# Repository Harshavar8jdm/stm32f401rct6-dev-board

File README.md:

# STM32F401RCT6 Development Board

A compact development board built around the STM32F401RCT6 microcontroller. The design provides access to core peripherals via standard pin headers, incorporates dedicated power plane isolation for analog stability, and includes robust ESD protection for reliable USB communication. 

## Visuals

### Schematic Diagram

### PCB Layout

### 3D Renders
| Front View | Back View |
| :---: | :---: |
|  |  |

---

## Features

### 1. Core Processing & Clock System
* **Microcontroller:** STM32F401RCT6, 32-bit ARM Cortex-M4 core running up to 84 MHz.
* **High-Speed External (HSE) Clock:** $25\text{ MHz}$ crystal oscillator loop supplying the primary system and peripheral clock source.
* **Low-Speed External (LSE) Clock:** $32.768\text{ kHz}$ tuning-fork crystal providing timing for the internal Real-Time Clock (RTC).
* **Reset & Boot Controls:** Hardware reset circuitry utilizing an RC network connected to the `NRST` pin, paired with a dedicated physical push-button to pull `BOOT0` high for system bootloader entry.

### 2. Power Delivery & Noise Mitigation
* **Voltage Regulation:** AMS1117-3.3 Linear Voltage Regulator (LDO) stepping down a $5\text{V}$ input supply (via USB) to a regulated $+3.3\text{V}$ system rail, decoupled with dual $22\ \mu\text{F}$ bulk capacitors.
* **Digital Rail Decoupling:** Localized filtering network consisting of one $4.7\ \mu\text{F}$ bulk capacitor and five independent $100\text{ nF}$ capacitors dedicated to the $V_{DD}$ supply pins.
* **Analog Isolation ($+3.3\text{VA}$):** A $100\ \Omega$ (at $100\text{ MHz}$) ferrite bead creates a low-pass filter to separate the analog supply from digital switching noise, supported by dedicated $1\ \mu\text{F}$ and $100\text{ nF}$ capacitors.

### 3. Connectivity & Protection
* **USB-C Interface:** USB 2.0 downstream configuration over a physical USB-C connector using dual $5.1\text{ k}\Omega$ pulldown resistors on the `CC1` and `CC2` channels.
* **Transient Voltage Protection:** A USBLC6-2SC6 monolithic ESD protection diode array is placed directly on the `USB_D+` and `USB_D-` lines to safeguard internal transceivers against electrostatic discharge.
* **Peripheral Access:** Dedicated pin headers breaking out SPI (`SPI3`), I2C (`I2C2`), UART (`UART1`), Serial Wire Debug (`SWD`), and generic GPIOs.
* **System Status:** Physical LED indicators tracking power availability ($+3.3\text{V}$) and a user-programmable diagnostic LED linked to pin `PA0`.

---

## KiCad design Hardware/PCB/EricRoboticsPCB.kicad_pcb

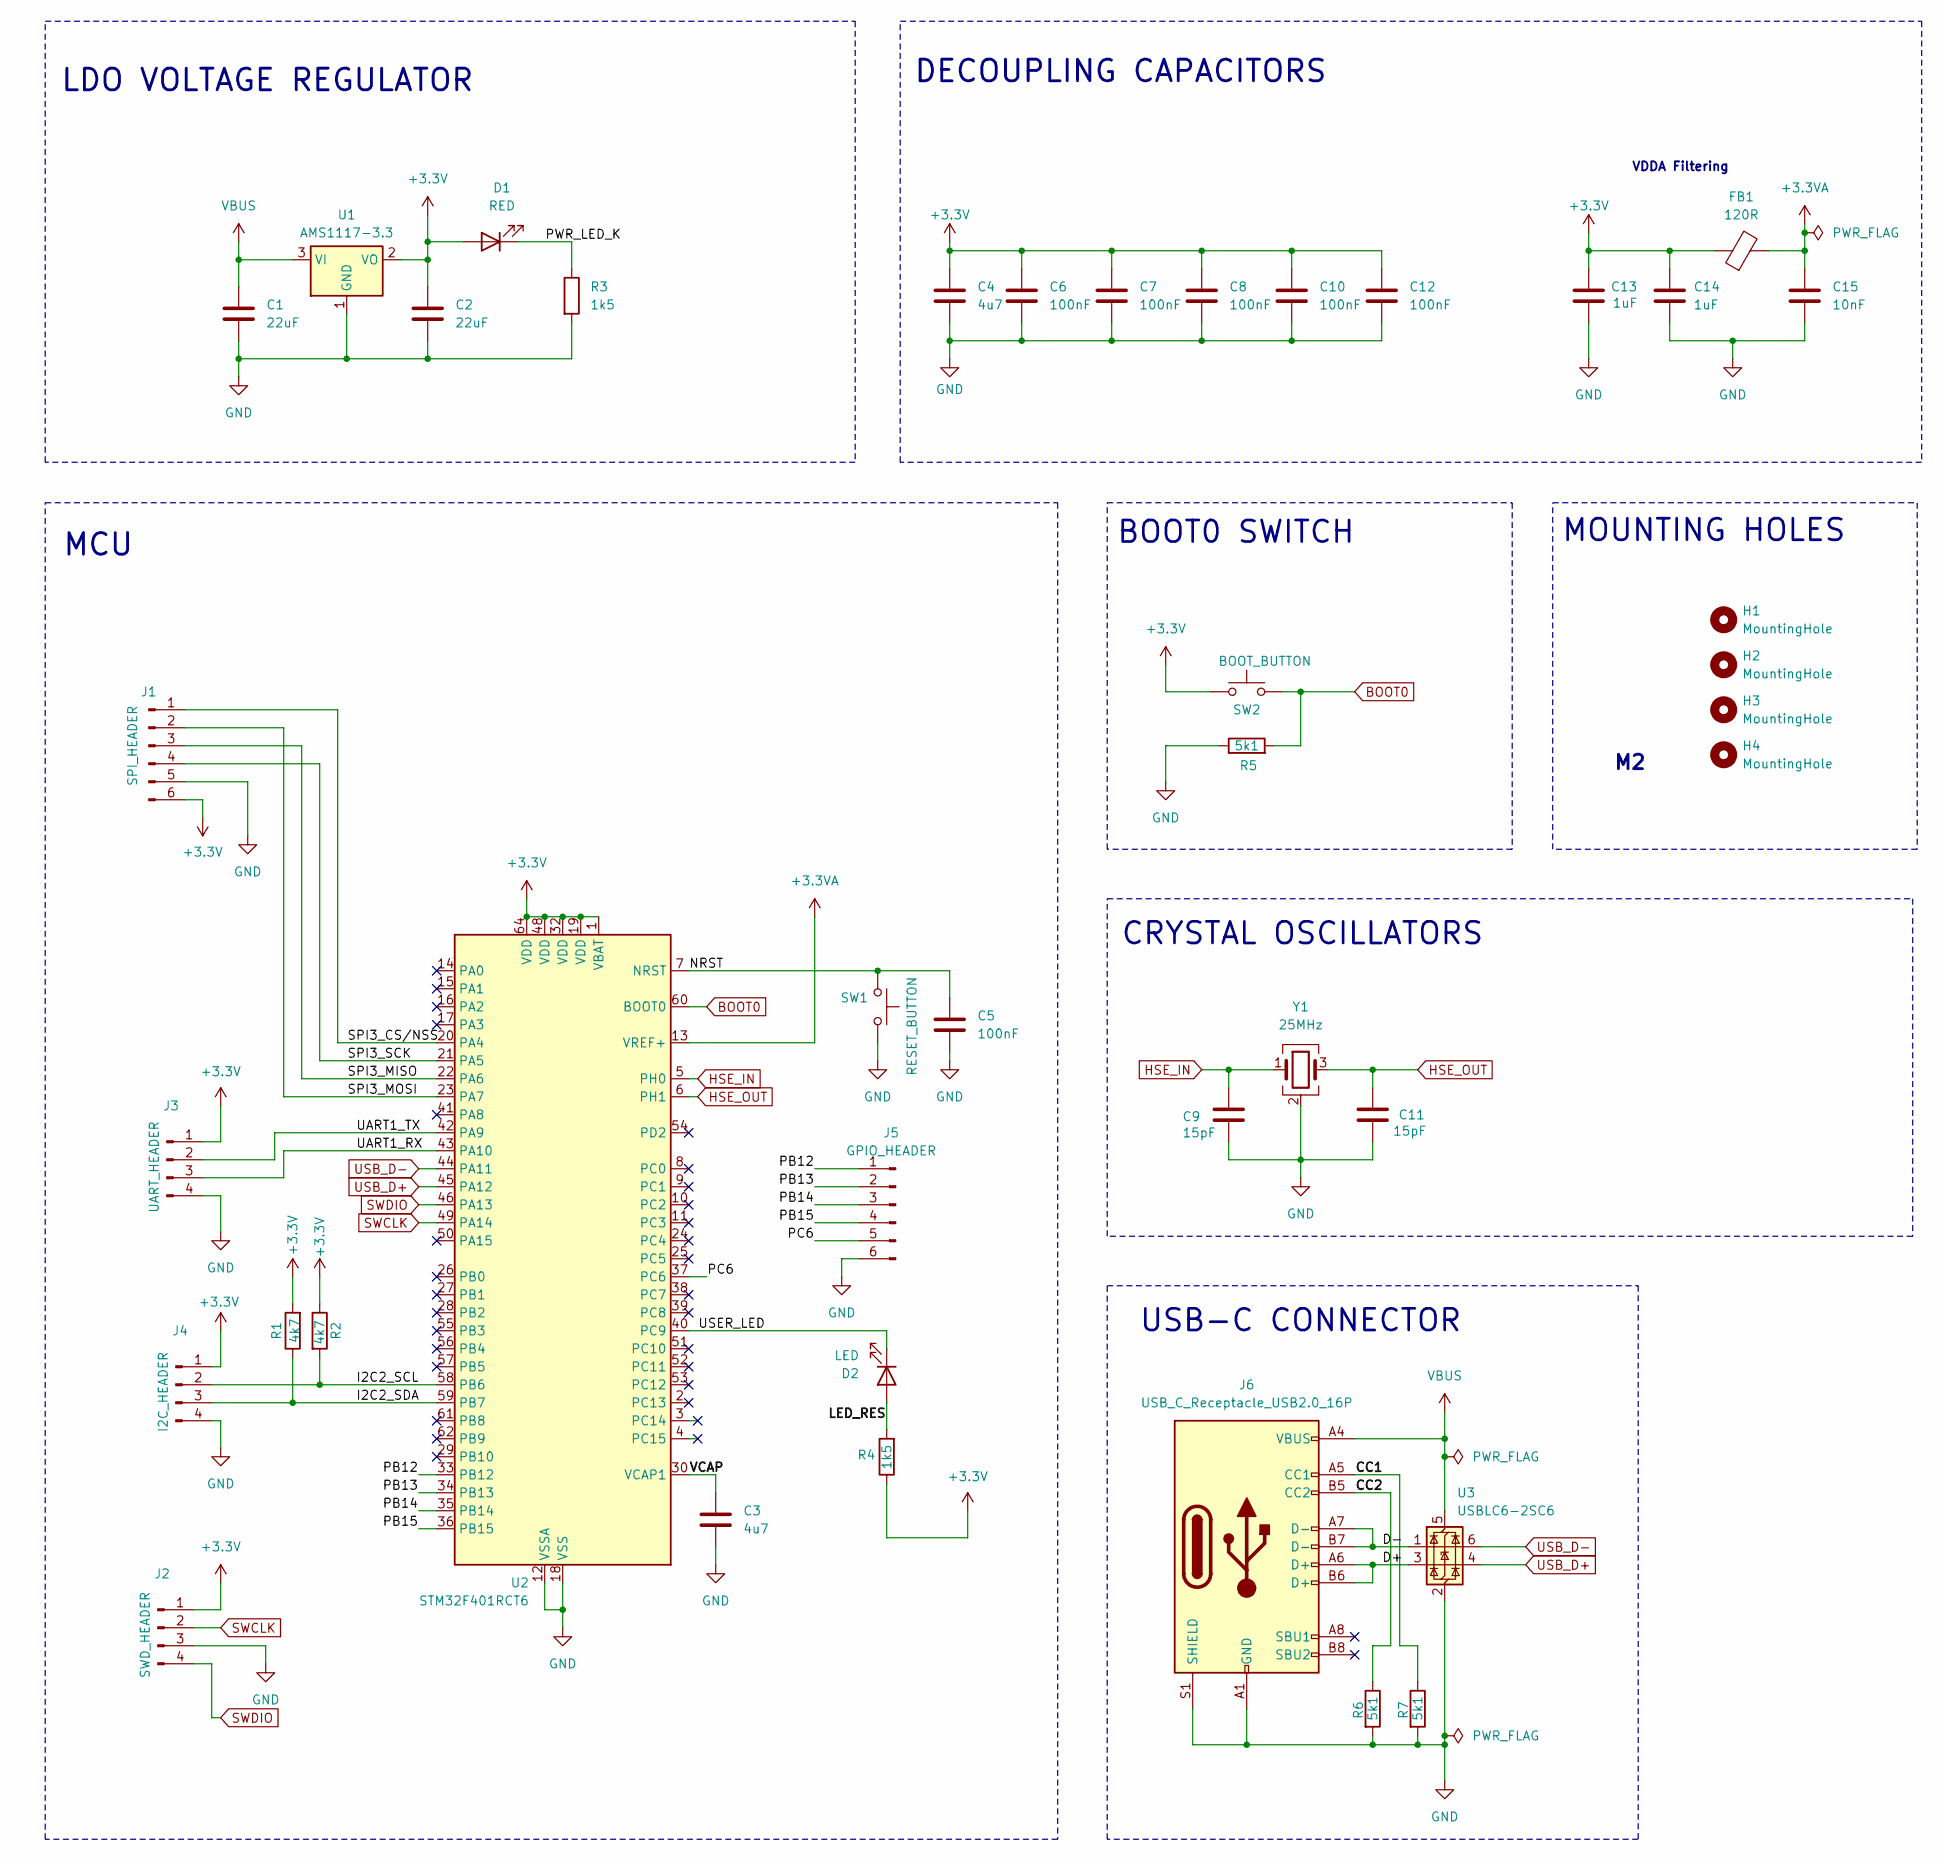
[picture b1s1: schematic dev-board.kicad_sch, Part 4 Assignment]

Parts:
C1, C2: 22uF; C_0805_2012Metric
C3, C4: 4u7; C_0805_2012Metric
C5, C6, C7, C8, C10, C12: 100nF; C_0402_1005Metric
C9, C11: 15pF; C_0402_1005Metric
C13, C14: 1uF; C_0402_1005Metric
C15: 10nF; C_0402_1005Metric
D1: RED; LED_0603_1608Metric
D2: LED; LED_0603_1608Metric
FB1: 120R; L_0603_1608Metric
H1, H2, H3, H4: MountingHole; MountingHole_2.2mm_M2
J1: SPI_HEADER; PinHeader_1x06_P2.54mm_Vertical
J2: SWD_HEADER; PinHeader_1x04_P2.54mm_Vertical
J3: UART_HEADER; PinHeader_1x04_P2.54mm_Vertical
J4: I2C_HEADER; PinHeader_1x04_P2.54mm_Vertical
J5: GPIO_HEADER; PinHeader_1x06_P2.54mm_Vertical
J6: USB_C_Receptacle_USB2.0_16P; USB_C_Receptacle_HRO_TYPE-C-31-M-12
R1, R2: 4k7; R_0402_1005Metric
R3, R4: 1k5; R_0402_1005Metric
R5, R6, R7: 5k1; R_0402_1005Metric
SW1: RESET_BUTTON; SW_Push_SPST_NO_Alps_SKRK
SW2: BOOT_BUTTON; SW_Push_SPST_NO_Alps_SKRK
U1: AMS1117-3.3; SOT-223-3_TabPin2
U2: STM32F401RCT6; LQFP-64_10x10mm_P0.5mm
U3: USBLC6-2SC6; SOT-23-6
Y1: 25MHz; Crystal_SMD_3225-4Pin_3.2x2.5mm

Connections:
+3.3V: C2.1, C4.1, C6.1, C7.1, C8.1, C10.1, C12.1, C13.1, C14.1, D1.2 (A), FB1.1, J1.6, J2.1, J3.1, J4.1, R1.2, R2.1, R4.1, SW2.2, U1.2 (VO), U2.1 (VBAT), U2.19 (VDD), U2.32 (VDD), U2.48 (VDD), U2.64 (VDD); also elsewhere on the board
+3.3VA: C15.1, FB1.2, U2.13 (VREF+)
/CC1: J6.A5 (CC1), R7.1
/CC2: J6.B5 (CC2), R6.1
/D+: J6.A6 (D+), J6.B6 (D+), U3.3 (I/O2)
/D-: J6.A7 (D-), J6.B7 (D-), U3.1 (I/O1)
/I2C2_SCL: J4.2, R2.2, U2.58 (PB6)
/I2C2_SDA: J4.3, R1.1, U2.59 (PB7)
/LED_RES: D2.2 (A), R4.2; also elsewhere on the board
/NRST: C5.1, SW1.2, U2.7 (NRST); also elsewhere on the board
/PB12: J5.1, U2.33 (PB12)
/PB13: J5.2, U2.34 (PB13)
/PB14: J5.3, U2.35 (PB14)
/PB15: J5.4, U2.36 (PB15)
/PC6: J5.5, U2.37 (PC6)
/PWR_LED_K: D1.1 (K), R3.1
/SPI3_CS/NSS: J1.1, U2.20 (PA4)
/SPI3_MISO: J1.3, U2.22 (PA6)
/SPI3_MOSI: J1.2, U2.23 (PA7)
/SPI3_SCK: J1.4, U2.21 (PA5)
/UART1_RX: J3.3, U2.43 (PA10)
/UART1_TX: J3.2, U2.42 (PA9)
/USER_LED: D2.1 (K), U2.40 (PC9); also elsewhere on the board
/VCAP: C3.1, U2.30 (VCAP1)
BOOT0: R5.2, SW2.1, U2.60 (BOOT0); also elsewhere on the board
GND: C1.2, C2.2, C3.2, C4.2, C5.2, C6.2, C7.2, C8.2, C9.2, C10.2, C11.2, C12.2, C13.2, C14.2, C15.2, J1.5, J2.3, J3.4, J4.4, J5.6, J6.A1 (GND), J6.A12 (GND), J6.B1 (GND), J6.B12 (GND), J6.S1 (SHIELD), R3.2, R5.1, R6.2, R7.2, SW1.1, U1.1 (GND), U2.12 (VSSA), U2.18 (VSS), U2.31 (VSS), U2.47 (VSS), U2.63 (VSS), U3.2 (GND), Y1.2 (G), Y1.4 (G); also elsewhere on the board
HSE_IN: C9.1, U2.5 (PH0), Y1.1
HSE_OUT: C11.1, U2.6 (PH1), Y1.3
SWCLK: J2.2, U2.49 (PA14)
SWDIO: J2.4, U2.46 (PA13)
USB_D+: U2.45 (PA12), U3.4 (I/O2)
USB_D-: U2.44 (PA11), U3.6 (I/O1)
VBUS: C1.1, J6.A4 (VBUS), J6.A9 (VBUS), J6.B4 (VBUS), J6.B9 (VBUS), U1.3 (VI), U3.5 (VBUS)

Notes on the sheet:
LDO VOLTAGE REGULATOR
MOUNTING HOLES
BOOT0 SWITCH
MCU
USB-C CONNECTOR
DECOUPLING CAPACITORS
CRYSTAL OSCILLATORS
VDDA Filtering

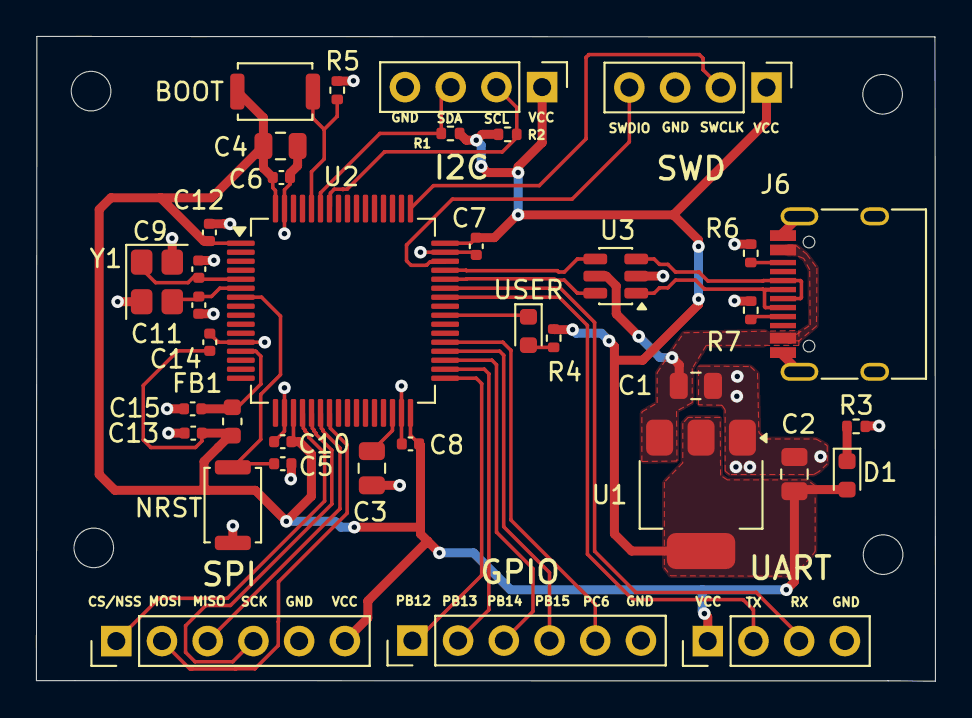
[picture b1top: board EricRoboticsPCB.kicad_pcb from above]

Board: 2 copper layers, 49.9 x 35.8 mm, 41 parts (0 on the bottom side), 33 nets.

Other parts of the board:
BOOT: BOOT_BUTTON; SW_Push_SPST_NO_Alps_SKRK
NRST: RESET_BUTTON; SW_Push_SPST_NO_Alps_SKRK
USER: LED; LED_0603_1608Metric

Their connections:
+3.3V: BOOT.2; also elsewhere on the board
/LED_RES: USER.2 (A); also elsewhere on the board
/NRST: NRST.2; also elsewhere on the board
/USER_LED: USER.1 (K); also elsewhere on the board
BOOT0: BOOT.1; also elsewhere on the board
GND: NRST.1; also elsewhere on the board
